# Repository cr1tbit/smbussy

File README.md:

## SMBusSY - USB to SMBus adapter

This simple board is an answer to mild CP2112 adapters shortage.

Nothing fancy, just pins breakout, and discrette 3.3V LDO for powering external projects.

I'll add some photos when the PCBs will arrive.

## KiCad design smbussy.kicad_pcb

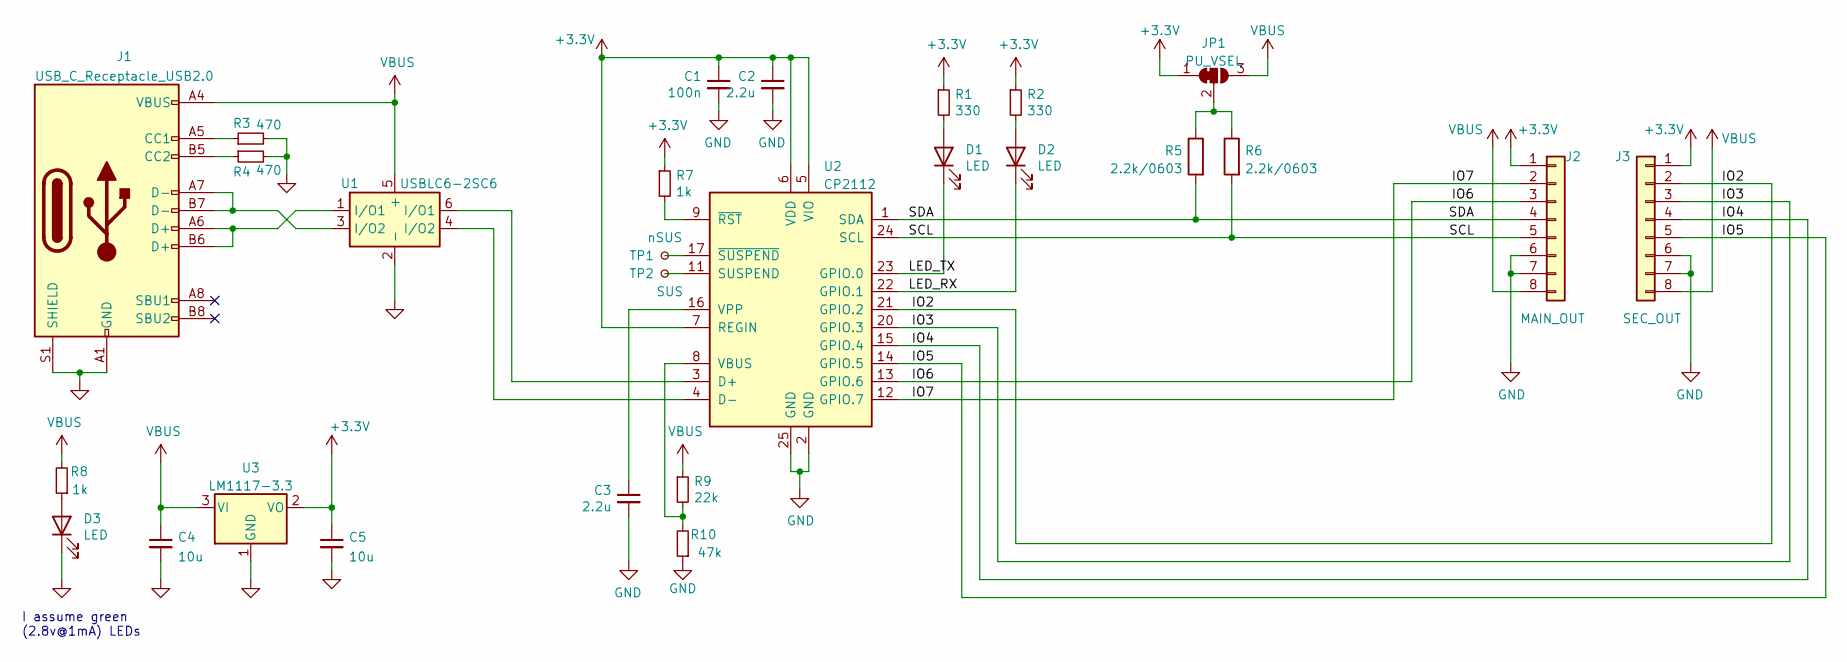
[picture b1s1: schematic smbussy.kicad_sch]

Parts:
C1: 100n; C_0402_1005Metric; LCSC C1525
C2, C3: 2.2u; C_0402_1005Metric; LCSC C12530
C4, C5: 10u; C_0603_1608Metric; LCSC C19702
D1, D2, D3: LED; LED_0603_1608Metric; LCSC C72043
J1: USB_C_Receptacle_USB2.0; USB_C_Receptacle_HRO_TYPE-C-31-M-12; LCSC C165948
J2: MAIN_OUT; PinHeader_1x08_P2.54mm_Vertical; LCSC C0000
J3: SEC_OUT; PinHeader_1x08_P2.54mm_Vertical; LCSC C0000
JP1: PU_VSEL; SolderJumper-3_P1.3mm_Bridged12_RoundedPad1.0x1.5mm
R1, R2: 330; R_0402_1005Metric; LCSC C25104
R3, R4: 470; R_0402_1005Metric; LCSC C25117
R5, R6: 2.2k/0603; R_0603_1608Metric_Pad0.98x0.95mm_HandSolder
R7, R8: 1k; R_0402_1005Metric; LCSC C11702
R9: 22k; R_0402_1005Metric; LCSC C25768
R10: 47k; R_0402_1005Metric; LCSC C25792
TP1: nSUS; TestPoint_Pad_D1.0mm
TP2: SUS; TestPoint_Pad_D1.0mm
U1: USBLC6-2SC6; SOT-23-6; LCSC C2687116
U2: CP2112; QFN-24-1EP_4x4mm_P0.5mm_EP2.6x2.6mm
U3: LM1117-3.3; SOT-223-3_TabPin2

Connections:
+3V3: C1.1, C2.1, C5.1, J2.1, J3.1, JP1.1 (A), R1.1, R2.1, R7.1, U2.5 (VIO), U2.6 (VDD), U2.7 (REGIN), U3.2 (VO)
/IO2: J3.2, U2.21 (GPIO.2)
/IO3: J3.3, U2.20 (GPIO.3)
/IO4: J3.4, U2.15 (GPIO.4)
/IO5: J3.5, U2.14 (GPIO.5)
/IO6: J2.3, U2.13 (GPIO.6)
/IO7: J2.2, U2.12 (GPIO.7)
/LED_RX: D2.1 (K), U2.22 (GPIO.1)
/LED_TX: D1.1 (K), U2.23 (GPIO.0)
/SCL: J2.5, R6.2, U2.24 (SCL)
/SDA: J2.4, R5.2, U2.1 (SDA)
GND: C1.2, C2.2, C3.2, C4.2, C5.2, D3.1 (K), J1.A1 (GND), J1.A12 (GND), J1.B1 (GND), J1.B12 (GND), J1.S1 (SHIELD), J2.6, J2.7, J3.6, J3.7, R3.2, R4.2, R10.1, U1.2 (-), U2.2 (GND), U2.25 (GND), U3.1 (GND)
unnamed: C3.1, U2.16 (VPP)
unnamed: D1.2 (A), R1.2
unnamed: D2.2 (A), R2.2
unnamed: D3.2 (A), R8.1
unnamed: J1.A5 (CC1), R3.1
unnamed: J1.A6 (D+), J1.B6 (D+), U1.1 (I/O1)
unnamed: J1.A7 (D-), J1.B7 (D-), U1.3 (I/O2)
unnamed: J1.B5 (CC2), R4.1
unnamed: JP1.2 (C), R5.1, R6.1
unnamed: R7.2, U2.9 (~RST)
unnamed: R9.2, R10.2, U2.8 (VBUS)
unnamed: TP1.1, U2.17 (~SUSPEND)
unnamed: TP2.1, U2.11 (SUSPEND)
unnamed: U1.4 (I/O2), U2.4 (D-)
unnamed: U1.6 (I/O1), U2.3 (D+)
VBUS: C4.1, J1.A4 (VBUS), J1.A9 (VBUS), J1.B4 (VBUS), J1.B9 (VBUS), J2.8, J3.8, JP1.3 (B), R8.2, R9.1, U1.5 (+), U3.3 (VI)

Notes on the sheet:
I assume green (2.8v@1mA) LEDs

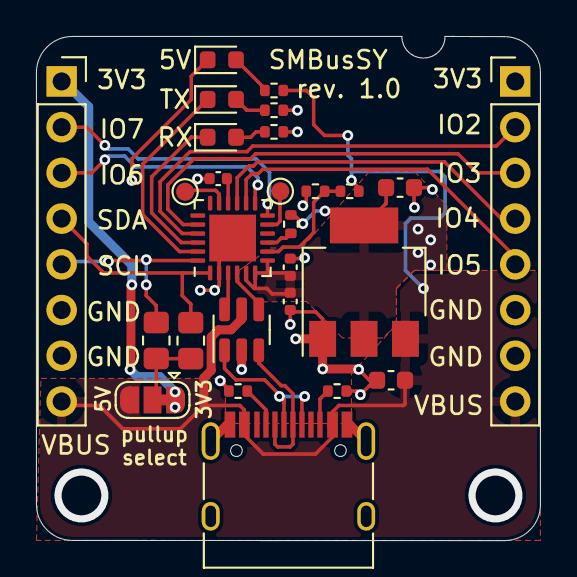
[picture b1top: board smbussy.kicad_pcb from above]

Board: 2 copper layers, 28.0 x 28.0 mm, 27 parts (0 on the bottom side), 28 nets.

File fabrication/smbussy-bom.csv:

Comment,Designator,Footprint,LCSC
100n,C1,Capacitor_SMD:C_0402_1005Metric,C1525
2.2u,"C2,C3",Capacitor_SMD:C_0402_1005Metric,C12530
10u,"C4,C5",Capacitor_SMD:C_0603_1608Metric,C19702
LED,"D1,D2,D3",LED_SMD:LED_0603_1608Metric,C72043
USB_C_Receptacle_USB2.0,J1,Connector_USB:USB_C_Receptacle_HRO_TYPE-C-31-M-12,C165948
MAIN_OUT,J2,Connector_PinHeader_2.54mm:PinHeader_1x08_P2.54mm_Vertical,C0000
SEC_OUT,J3,Connector_PinHeader_2.54mm:PinHeader_1x08_P2.54mm_Vertical,C0000
PU_VSEL,JP1,Jumper:SolderJumper-3_P1.3mm_Bridged12_RoundedPad1.0x1.5mm,C0000
330,"R1,R2",Resistor_SMD:R_0402_1005Metric,C25104
47k,R10,Resistor_SMD:R_0402_1005Metric,C25792
470,"R3,R4",Resistor_SMD:R_0402_1005Metric,C25117
2.2k/0603,"R5,R6",Resistor_SMD:R_0603_1608Metric_Pad0.98x0.95mm_HandSolder,C4190
1k,"R7,R8",Resistor_SMD:R_0402_1005Metric,C11702
22k,R9,Resistor_SMD:R_0402_1005Metric,C25768
nSUS,TP1,TestPoint:TestPoint_Pad_D1.0mm,C0000
SUS,TP2,TestPoint:TestPoint_Pad_D1.0mm,C0000
USBLC6-2SC6,U1,Package_TO_SOT_SMD:SOT-23-6,C2687116
CP2112,U2,Package_DFN_QFN:QFN-24-1EP_4x4mm_P0.5mm_EP2.6x2.6mm,C0000
LM1117-3.3,U3,Package_TO_SOT_SMD:SOT-223-3_TabPin2,C6186

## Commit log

2022-10-07 finish layout
2022-10-07 add fabrication outputs and readme and stuff
